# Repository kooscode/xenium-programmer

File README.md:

# OpenXenium JTAG and Flash Memory programmer

## * Read: ["Home Brew" on ORIGINAL XBOX](XBOX.md) - a detailed article on why and how *

The tools in this repo will allow you to use a Raspberry PI or an Onion Omega2+ to program an OpenXenium chip with the Xilinx CPLD Firmware via JTAG and will also upload XeniumOS images into the OpenXenium Flash memory via a custom 4-bit bus NOR Flash programming protocol. 

### Raspberry PI [UPDATED to support latest Raspberry PI OS (Bullseye)] :
- This has only been tested on PI Zero W and PI 3B+ model, but should work for all.

https://www.pishop.us/product/raspberry-pi-zero-w

https://www.pishop.us/product/raspberry-pi-zero-2-w

### Onion Omega2+:
- This has been tested and works on the Onion Omega2+.

https://Onion.io/store/omega2p

-------------
## INSTALLING THE XENIUM PROGRAMMER

- Connect to the PI or Omega via SSH or Serial terminal 
- Clone this repo by running: `git clone https://github.com/kooscode/xenium-programmer.git`
- Change Dir to cloned repo: `cd xenium-programmer`
- Then run: `./install`

## UPDATING XENIUM PROGRAMMER

- Connect to the PI or Omega via SSH or Serial terminal 
- Change dir to xenium-programmer and pull the latest code with: `git pull`
- Then run: `./install` 

-------------
## PROGRAMMING A XENIUM CPLD AND FLASH MEMORY

- Connect to the PI or Omega via SSH or Serial terminal 
- You can program XeniumOS and OpenXenium Firmware in one single step.
- Run: `./xenium-programmer`  

-------------
## HOOKING UP THE HARDWARE

- The JTAG and FLASH pins are configurable by editing the `XeniumDefines.h` file 
- If you edited the `XeniumDefines.h` file, make sure to run `./install` again

--------------
## [ RASPBERRY PI ]

### PC BOARD

Huge thanks to James Bolding for the Eagle PCB hardware design. He made a kick-ass Schematic and PCB that you can make for the Raspberry PI Zero based programmer!  

- You can use the FREE Eagle PCB to load this up or just use the gerber files to have the PCB made at OSH Park!

--------------
## [ ONION OMEGA2+ ]

-------------
## CREDITS

- Koos du Preez - Creator (kdupreez@hotmail.com - Comments, improvements, critique, etc. is welcome!)
- James Bolding - Kick ass awesome hardware design and PCB!
- Ryzee119 -  OpenXenium Firmware and hardware and all round awesomeness!
- XC3SPROG - Not sure who to thank here, but the source code was pivotal in making this work!

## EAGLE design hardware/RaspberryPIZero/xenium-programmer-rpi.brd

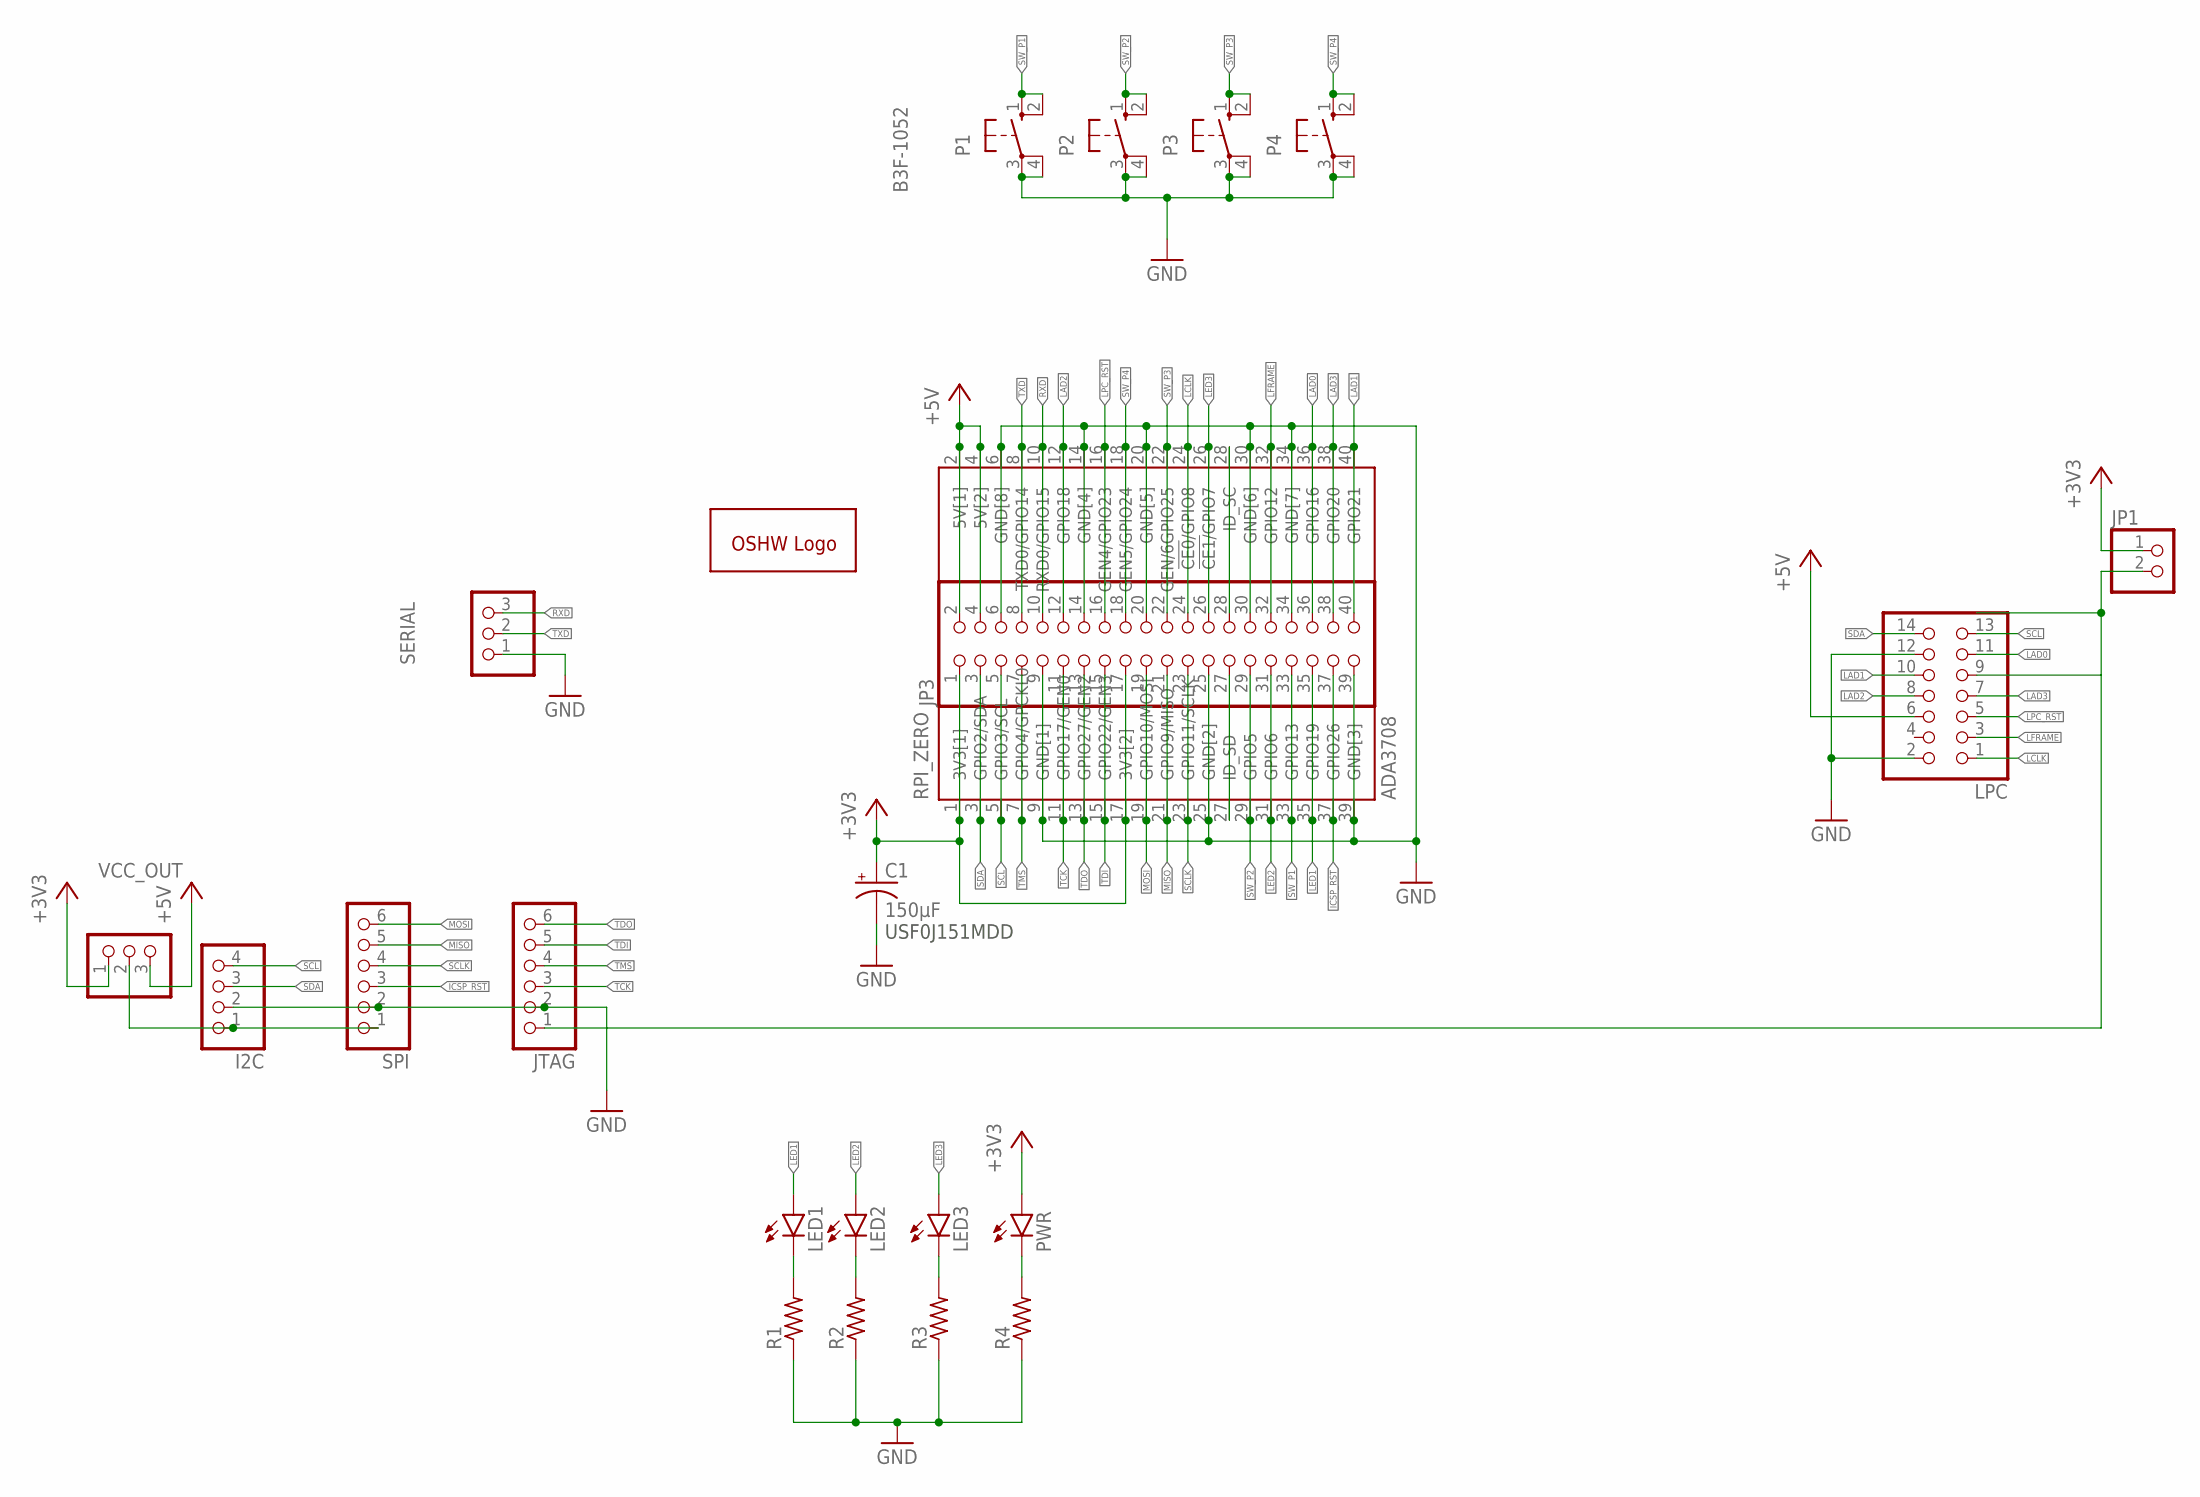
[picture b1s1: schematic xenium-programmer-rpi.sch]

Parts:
C1: 150µF; E3,5-8
GOLD_ORB_SM1: OSHWLOGOLOGO8MM; OSHW_8MM
I2C: PINHD-1X4; 1X04
JP1: PINHD-1X2; 1X02
JP3: PINHD-2X20; 2X20
JTAG: PINHD-1X6; 1X06
LED1, LED2, LED3: LED5MM
LPC: PINHD-2X7; 2X07
P1, P2, P3, P4: B3F-1052; B3F-10XX
PWR: LED5MM
R1, R2, R3, R4: R-US_0207/10; 0207/10
RPI_ZERO: ADA3708; ADA3708_RPI-ZERO
SERIAL: PINHD-1X3; 1X03
SPI: PINHD-1X6; 1X06
VCC_OUT: PINHD-1X3; 1X03

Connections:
+3V3: C1.+, JP1.1, JP3.1, JP3.17, PWR.A, RPI_ZERO.1 (3V3[1]), RPI_ZERO.17 (3V3[2]), VCC_OUT.1
+5V: JP3.2, JP3.4, LPC.6, RPI_ZERO.2 (5V[1]), RPI_ZERO.4 (5V[2]), VCC_OUT.3
GND: C1.-, I2C.2, JP3.6, JP3.9, JP3.14, JP3.20, JP3.25, JP3.30, JP3.34, JP3.39, JTAG.2, LPC.2, LPC.12, P1.3, P1.4 (P1), P2.3, P2.4 (P1), P3.3, P3.4 (P1), P4.3, P4.4 (P1), R1.1, R2.1, R3.1, R4.1, RPI_ZERO.6 (GND[8]), RPI_ZERO.9 (GND[1]), RPI_ZERO.14 (GND[4]), RPI_ZERO.20 (GND[5]), RPI_ZERO.25 (GND[2]), RPI_ZERO.30 (GND[6]), RPI_ZERO.34 (GND[7]), RPI_ZERO.39 (GND[3]), SERIAL.1, SPI.2
ICSP_RST: JP3.37, RPI_ZERO.37 (GPIO26), SPI.3
LAD0: JP3.36, LPC.11, RPI_ZERO.36 (GPIO16)
LAD1: JP3.40, LPC.10, RPI_ZERO.40 (GPIO21)
LAD2: JP3.12, LPC.8, RPI_ZERO.12 (GPIO18)
LAD3: JP3.38, LPC.7, RPI_ZERO.38 (GPIO20)
LCLK: JP3.24, LPC.1, RPI_ZERO.24 (!CE0!/GPIO8)
LED1: JP3.35, LED1.A, RPI_ZERO.35 (GPIO19)
LED2: JP3.31, LED2.A, RPI_ZERO.31 (GPIO6)
LED3: JP3.26, LED3.A, RPI_ZERO.26 (!CE1/!GPIO7)
LFRAME: JP3.32, LPC.3, RPI_ZERO.32 (GPIO12)
LPC_RST: JP3.16, LPC.5, RPI_ZERO.16 (GEN4/GPIO23)
MISO: JP3.21, RPI_ZERO.21 (GPIO9/MISO), SPI.5
MOSI: JP3.19, RPI_ZERO.19 (GPIO10/MOSI), SPI.6
unnamed: LED1.K (C), R1.2
unnamed: JP3.27, RPI_ZERO.27 (ID_SD)
unnamed: LED2.K (C), R2.2
unnamed: LED3.K (C), R3.2
unnamed: PWR.K (C), R4.2
unnamed: JP1.2, JTAG.1, LPC.9
unnamed: JP3.28, RPI_ZERO.28 (ID_SC)
RXD: JP3.10, RPI_ZERO.10 (RXD0/GPIO15), SERIAL.3
SCL: I2C.4, JP3.5, LPC.13, RPI_ZERO.5 (GPIO3/SCL)
SCLK: JP3.23, RPI_ZERO.23 (GPIO11/SCLK), SPI.4
SDA: I2C.3, JP3.3, LPC.14, RPI_ZERO.3 (GPIO2/SDA)
SW_P1: JP3.33, P1.1 (S), P1.2 (S1), RPI_ZERO.33 (GPIO13)
SW_P2: JP3.29, P2.1 (S), P2.2 (S1), RPI_ZERO.29 (GPIO5)
SW_P3: JP3.22, P3.1 (S), P3.2 (S1), RPI_ZERO.22 (GEN/6GPIO25)
SW_P4: JP3.18, P4.1 (S), P4.2 (S1), RPI_ZERO.18 (GEN5/GPIO24)
TCK: JP3.11, JTAG.3, RPI_ZERO.11 (GPIO17/GEN0)
TDI: JP3.15, JTAG.5, RPI_ZERO.15 (GPIO22/GEN3)
TDO: JP3.13, JTAG.6, RPI_ZERO.13 (GPIO27/GEN2)
TMS: JP3.7, JTAG.4, RPI_ZERO.7 (GPIO4/GPCKL0)
TXD: JP3.8, RPI_ZERO.8 (TXD0/GPIO14), SERIAL.2
VCC_OUT: I2C.1, SPI.1, VCC_OUT.2

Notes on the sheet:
USF0J151MDD

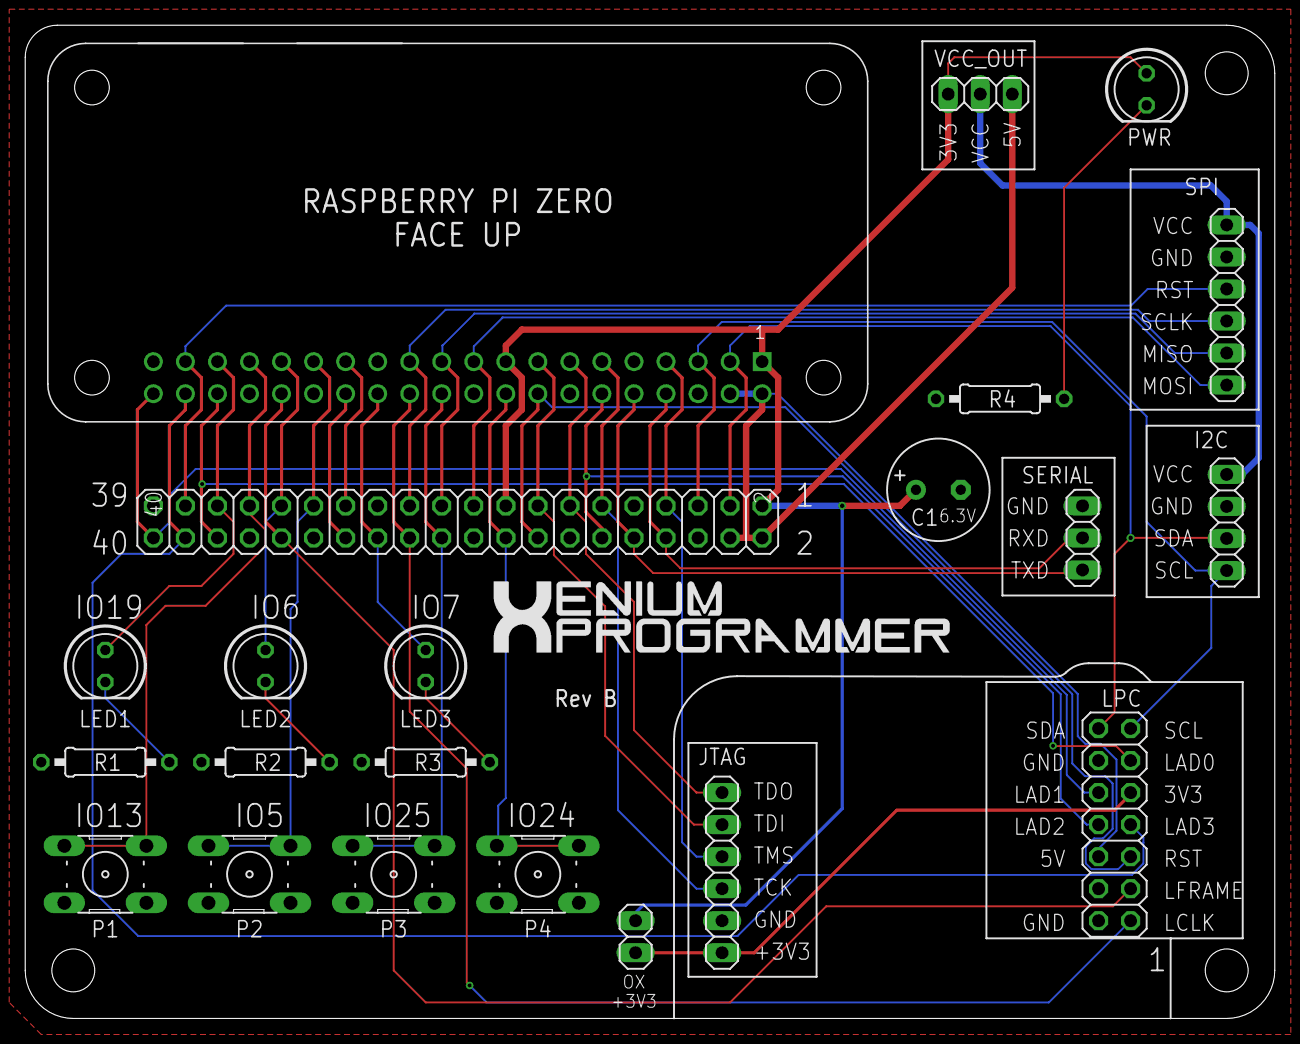
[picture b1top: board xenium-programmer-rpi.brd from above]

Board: 2 copper layers, 99.1 x 78.7 mm, 23 parts (1 on the bottom side), 37 nets.

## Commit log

2020-12-30 first commit :)
2020-12-30 readme update
2020-12-30 gpio delay woes.. :s
2020-12-30 adding xenium bins :)
2020-12-30 cosmetics
2020-12-30 huge readme update
2020-12-30 readme updates
2020-12-30 install +X
2020-12-30 fix updsidedown img
2020-12-31 img update
2020-12-31 Fixed some typos
2021-01-01 comments update
2021-01-02 removed xc3sprog
2021-01-02 added licensing
2021-01-02 sshot update
2021-01-02 small edits
2021-01-03 Update xenium-programmer
2021-01-03 simplified instructions..
2021-01-03 use default blue XeniumOS
2021-01-03 using default blue XeniumOS
2021-01-03 Testing webhook integration
2021-01-06 pi style gpio
2021-01-06 omega2+ install issue
2021-01-06 updated description
2021-01-06 removed debug build
2021-01-06 less confusing ifndef vs ifdef :)
2021-01-06 test protected main branch
2021-01-09 added RPI PCB
2021-01-13 added omega2+ pinouts
2021-01-15 added cmdline switch to not ask for erase/flash
2021-01-15 check for blank CPLD when flashing
2021-01-15 small typos
2021-01-20 Added C1 on RPI PCB to prevent brownout caused by OX LED sometimes, added jumper to control +3v3 for OX chips. Moved RPI PCB to Rev B
2021-01-22 re-mapped GPIO8 and GPIO24
2021-01-23 Update install
    Commented out update for old programmer pcb
2021-01-23 rpi board update
2021-01-25 Updated install script to detect whether the system is un-supported, and allow for a fallback to compile it anyway with the expert flag
2021-01-29 install script bug
2022-07-03 Added experimental Python wrapper for Pi-Zero Board with LED support
2022-07-04 Update xenium-programmer-pi
2022-07-22 Update xenium-flash.cpp
    To mimic the same check in xenium-tools to verify the flash is ready for the next write, otherwise it will be ignored and could fail verify.
2023-01-01 RPI-OS Support
2023-01-01 made install executable
2023-01-07 Add check to verify next block ready to write
    Added a check during the write phase to verify the flash is ready before moving to next block. The fixes issues programming original AMD AM29LV160MT-100EI and some troublesome Spansion S29AL016J70TFI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
2023-01-07 Fix formatting
2023-01-26 Update xenium-flash.cpp
    Add flash check for Macronix MX29LV160DB
2023-01-26 Update xenium-flash.cpp
    Update flash detection output with "Macronix"
2023-01-26 Update xenium-flash.cpp
    Fix order of if loop to execute check for Macronix before flash detection error step

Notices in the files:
hardware/RaspberryPIZero/xenium-programmer-rpi.brd:
Released under
CERN OHL v1.2
